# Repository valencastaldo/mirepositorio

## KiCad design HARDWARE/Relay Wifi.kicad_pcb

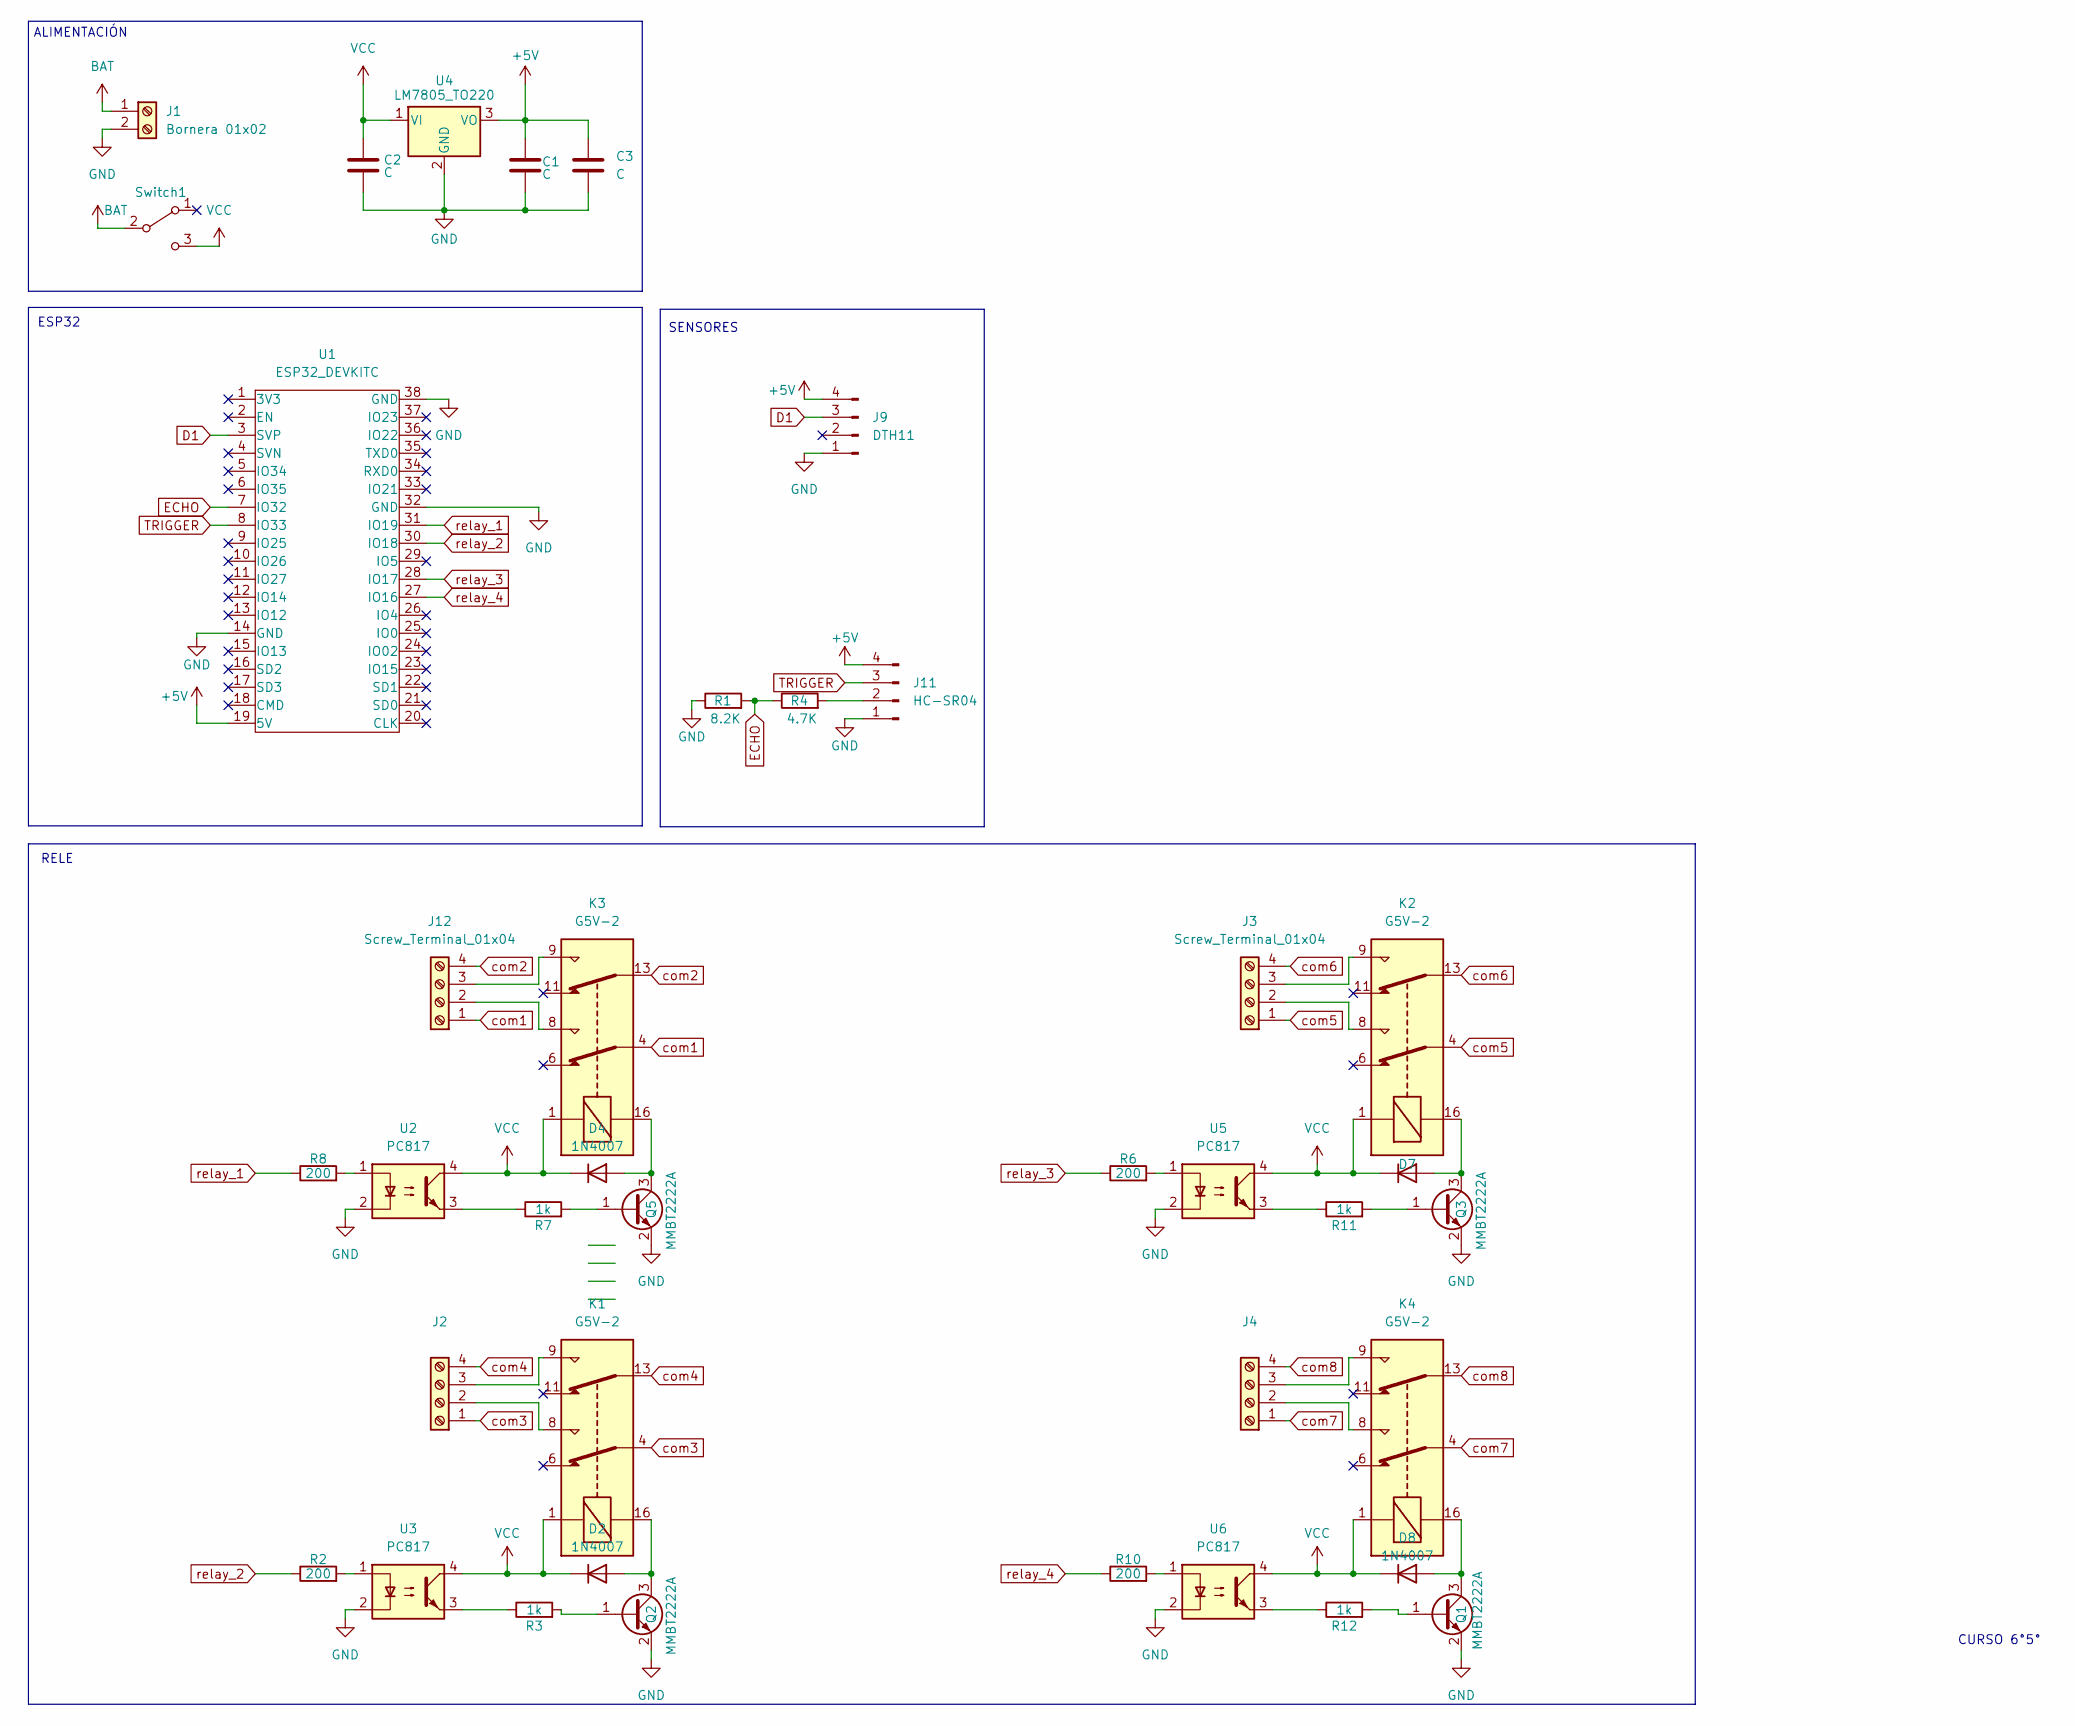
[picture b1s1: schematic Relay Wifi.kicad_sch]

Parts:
C1, C2: C; C_0805_2012Metric_Pad1.18x1.45mm_HandSolder
C3: C; CP_Elec_10x10
D2, D4, D7, D8: 1N4007; D_SMA
J1: Bornera 01x02; TerminalBlock_bornier-2_P5.08mm
J2, J3, J4, J12: Screw_Terminal_01x04; Altech_AK100_1x04_P5.00mm
J9: DTH11; pin_strip_4
J11: HC-SR04; pin_strip_4
K1, K2, K3, K4: G5V-2; Relay_DPDT_Omron_G5V-2
Q1, Q2, Q3, Q5: MMBT2222A; SOT-23
R1: 8.2K; R_0805_2012Metric_Pad1.20x1.40mm_HandSolder
R2, R6, R8, R10: 200; R_0805_2012Metric_Pad1.20x1.40mm_HandSolder
R3, R7, R11, R12: 1k; R_0805_2012Metric_Pad1.20x1.40mm_HandSolder
R4: 4.7K; R_0805_2012Metric_Pad1.20x1.40mm_HandSolder
Switch1: SW_SPDT; TerminalBlock_bornier-3_P5.08mm
U1: ESP32_DEVKITC
U2, U3, U5, U6: PC817; DIP-4_PC817
U4: LM7805_TO220; TO-263-3_TabPin2

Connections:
+5V: C1.1, C3.1, J9.4, J11.4, U1.19 (5V), U4.3 (VO)
BAT: J1.1, Switch1.2 (B)
D1: J9.3, U1.3 (SVP)
ECHO: R1.2, R4.1, U1.7 (IO32)
GND: C1.2, C2.2, C3.2, J1.2, J9.1, J11.1, Q1.2 (E), Q2.2 (E), Q3.2 (E), Q5.2 (E), R1.1, U1.14 (GND), U1.32 (GND), U1.38 (GND), U2.2, U3.2, U4.2 (GND), U5.2, U6.2
unnamed: D2.2 (A), K1.16, Q2.3 (C)
unnamed: D4.2 (A), K3.16, Q5.3 (C)
unnamed: D7.2 (A), K2.16, Q3.3 (C)
unnamed: D8.2 (A), K4.16, Q1.3 (C)
unnamed: J2.2, K1.8
unnamed: J2.3, K1.9
unnamed: J3.2, K2.8
unnamed: J3.3, K2.9
unnamed: J4.2, K4.8
unnamed: J4.3, K4.9
unnamed: J11.2, R4.2
unnamed: J12.2, K3.8
unnamed: J12.3, K3.9
unnamed: Q1.1 (B), R12.2
unnamed: Q2.1 (B), R3.2
unnamed: Q3.1 (B), R11.2
unnamed: Q5.1 (B), R7.2
unnamed: R2.2, U3.1
unnamed: R3.1, U3.3
unnamed: R6.2, U5.1
unnamed: R7.1, U2.3
unnamed: R8.2, U2.1
unnamed: R10.2, U6.1
unnamed: R11.1, U5.3
unnamed: R12.1, U6.3
TRIGGER: J11.3, U1.8 (IO33)
VCC: C2.1, D2.1 (K), D4.1 (K), D7.1 (K), D8.1 (K), K1.1, K2.1, K3.1, K4.1, Switch1.3 (C), U2.4, U3.4, U4.1 (VI), U5.4, U6.4
com1: J12.1, K3.4
com2: J12.4, K3.13
com3: J2.1, K1.4
com4: J2.4, K1.13
com5: J3.1, K2.4
com6: J3.4, K2.13
com7: J4.1, K4.4
com8: J4.4, K4.13
relay_1: R8.1, U1.31 (IO19)
relay_2: R2.1, U1.30 (IO18)
relay_3: R6.1, U1.28 (IO17)
relay_4: R10.1, U1.27 (IO16)

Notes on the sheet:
SENSORES
CURSO 6°5°
RELE
ESP32
ALIMENTACIÓN

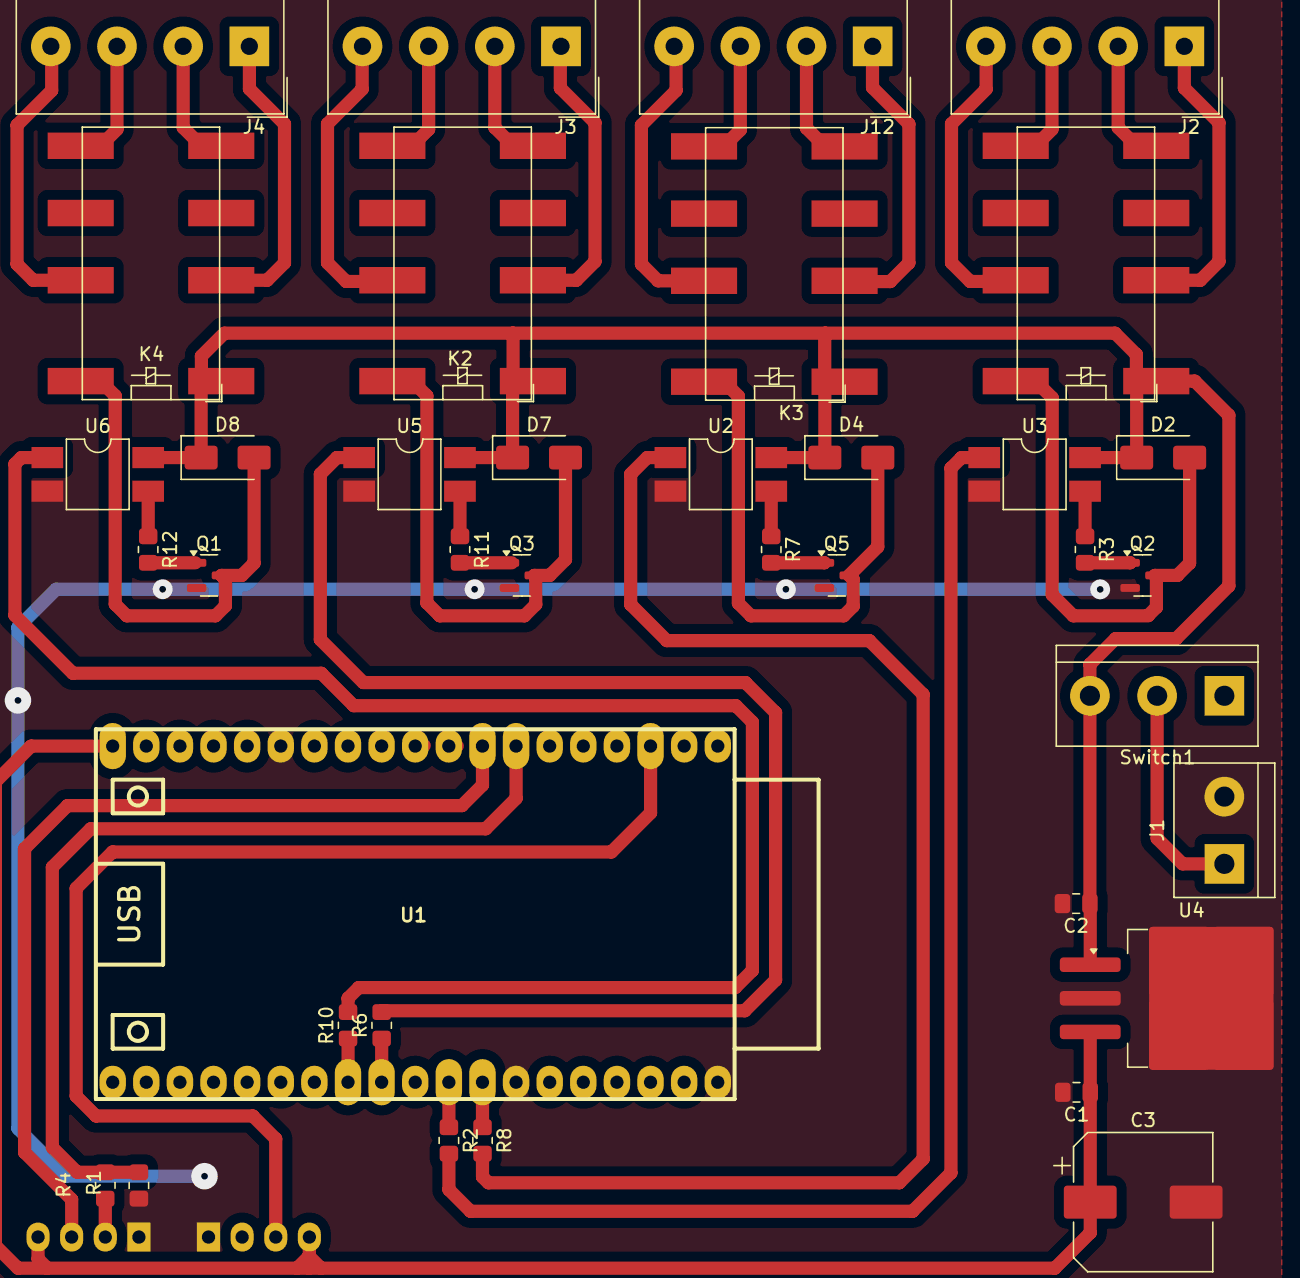
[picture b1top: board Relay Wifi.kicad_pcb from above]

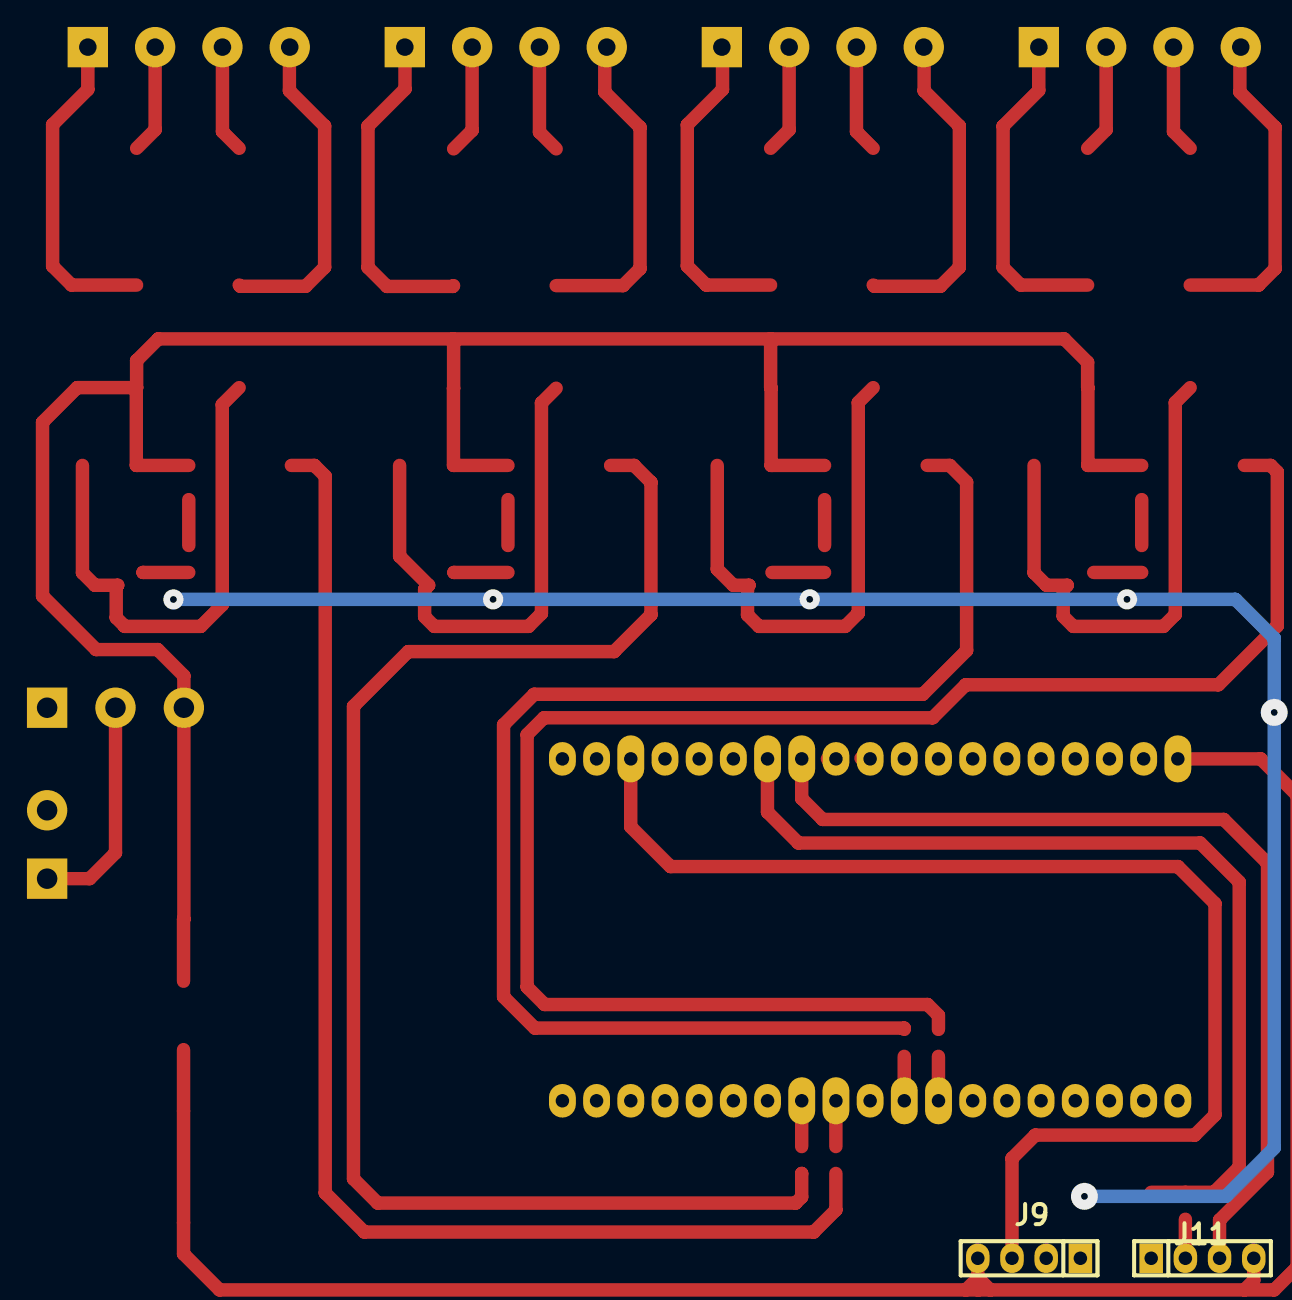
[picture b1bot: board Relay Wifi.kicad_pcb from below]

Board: 2 copper layers, 39 parts (2 on the bottom side), 44 nets.

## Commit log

2025-04-06 Mi primer commit
2025-04-06 Modificamos titulo en index.html
2025-05-11 Agrego carpeta HARDWARE
2025-05-11 Agrego Carpetas SOFTWARE Y 3D
2025-05-11 Agrego archivo README.md
2025-05-11 Eliminado archivo index.html
2025-05-13 Eliminado archivo de esquema no actualizado Relay Wifi.kicad_sch
2025-05-13 Agregado esquematico actualizado del Relay Wifi en la carpeta HARDWARE
2025-05-26 Actualizo el esquematico
2025-06-06 Agrego carpeta hardware con archivos
2025-06-06 Agrego el nuevo diseño de la placa y el esquematico
